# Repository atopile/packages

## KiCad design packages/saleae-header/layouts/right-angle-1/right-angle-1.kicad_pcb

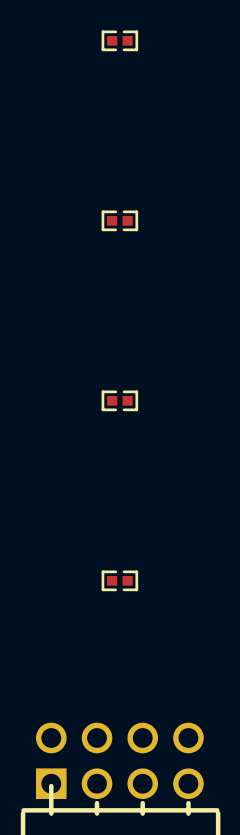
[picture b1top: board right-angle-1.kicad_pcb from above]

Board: 2 copper layers, 5 parts (0 on the bottom side), 5 nets, no tracks yet.

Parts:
R1, R2, R3, R4: 1kΩ ±1% 62.5mW; R0402
U1: HDR-TH_8P-P2.54-H-F-R2-C4-W8.5

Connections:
gnd: U1.2, U1.4, U1.6, U1.8
pins[0]: R1.2, U1.1
pins[2]: R2.2, U1.3
pins[4]: R3.2, U1.5
pins[6]: R4.2, U1.7

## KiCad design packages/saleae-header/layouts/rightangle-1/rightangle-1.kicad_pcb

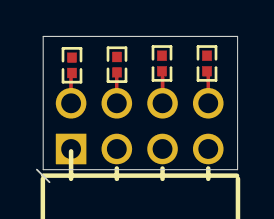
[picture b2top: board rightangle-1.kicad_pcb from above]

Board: 2 copper layers, 11.2 x 8.1 mm, 5 parts (0 on the bottom side), 5 nets.

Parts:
R1, R2, R3, R4: 1000Ω; R0402
U1: HDR-TH_8P-P2.54-H-F-R2-C4-W8.5

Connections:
2: R1.2, U1.2
4: R2.2, U1.4
6: R3.2, U1.6
8: R4.2, U1.8
lv: U1.1, U1.3, U1.5, U1.7

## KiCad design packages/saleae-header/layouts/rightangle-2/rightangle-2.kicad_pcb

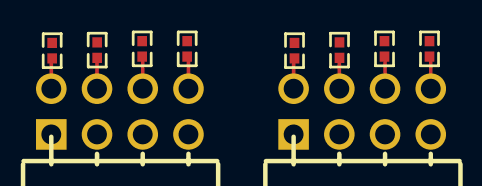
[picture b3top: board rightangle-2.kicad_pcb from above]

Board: 2 copper layers, 10 parts (0 on the bottom side), 10 nets.

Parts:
R1, R2, R3, R4, R5, R6, R7, R8: 1000Ω; R0402
U1, U2: HDR-TH_8P-P2.54-H-F-R2-C4-W8.5

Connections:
2: R1.2, U1.2
4: R2.2, U1.4
6: R3.2, U1.6
8: R4.2, U1.8
headers[1]-2: R5.2, U2.2
headers[1]-4: R6.2, U2.4
headers[1]-6: R7.2, U2.6
headers[1]-8: R8.2, U2.8
headers[1]-reference-lv: U2.1, U2.3, U2.5, U2.7
lv: U1.1, U1.3, U1.5, U1.7

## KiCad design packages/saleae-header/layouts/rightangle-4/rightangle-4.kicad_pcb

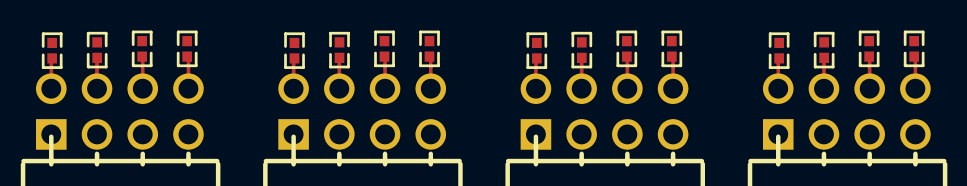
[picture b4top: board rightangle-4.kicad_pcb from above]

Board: 2 copper layers, 20 parts (0 on the bottom side), 20 nets.

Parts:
R1, R2, R3, R4, R5, R6, R7, R8, R9, R10, R11, R12, R13, R14, R15, R16: 1000Ω; R0402
U1, U2, U3, U4: HDR-TH_8P-P2.54-H-F-R2-C4-W8.5

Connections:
2: R1.2, U1.2
4: R2.2, U1.4
6: R3.2, U1.6
8: R4.2, U1.8
headers[1]-2: R5.2, U2.2
headers[1]-4: R6.2, U2.4
headers[1]-6: R7.2, U2.6
headers[1]-8: R8.2, U2.8
headers[1]-reference-lv: U2.1, U2.3, U2.5, U2.7
headers[2]-2: R9.2, U3.2
headers[2]-4: R10.2, U3.4
headers[2]-6: R11.2, U3.6
headers[2]-8: R12.2, U3.8
headers[2]-reference-lv: U3.1, U3.3, U3.5, U3.7
headers[3]-2: R13.2, U4.2
headers[3]-4: R14.2, U4.4
headers[3]-6: R15.2, U4.6
headers[3]-8: R16.2, U4.8
headers[3]-reference-lv: U4.1, U4.3, U4.5, U4.7
lv: U1.1, U1.3, U1.5, U1.7

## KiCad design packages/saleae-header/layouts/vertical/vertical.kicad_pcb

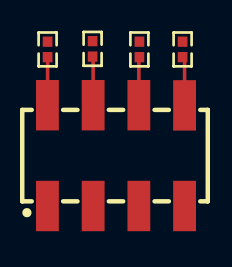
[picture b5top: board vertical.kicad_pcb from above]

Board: 2 copper layers, 5 parts (0 on the bottom side), 5 nets.

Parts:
HDR1: HDR-SMD_8P-P2.54-V-M-R2-C4-LS7.4
R1, R2, R3, R4: 1000Ω; R0402

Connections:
2: HDR1.2, R1.2
4: HDR1.4, R2.2
6: HDR1.6, R3.2
8: HDR1.8, R4.2
lv: HDR1.1, HDR1.3, HDR1.5, HDR1.7

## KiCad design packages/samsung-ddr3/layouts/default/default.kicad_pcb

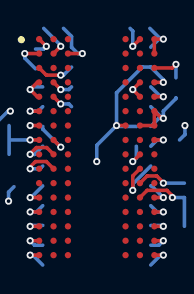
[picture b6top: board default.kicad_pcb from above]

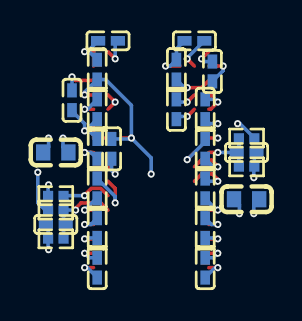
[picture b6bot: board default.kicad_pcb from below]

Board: 4 copper layers, 28 parts (27 on the bottom side), 6 nets.

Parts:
C1, C2, C5, C6, C7, C8, C9, C10, C11, C12, C13, C14, C15, C16, C17, C18, C19, C20, C21, C22: 100nF ±10% 6.3V X7R; C0402
C3, C4: 10µF ±20% 6.3V X5R; C0603
R1: 240Ω ±1% 62.5mW; R0402
R2, R3, R4, R5: 1kΩ ±1% 62.5mW; R0402
U1: TFBGA-96_L13.0-W7.5-R16-C6-P0.80-TL

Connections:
GND: C1.2, C2.2, C3.2, C4.2, C5.2, C6.2, C7.2, C8.2, C9.2, C10.2, C11.2, C12.2, C13.2, C14.2, C15.2, C16.2, C17.2, C18.2, C19.2, C20.2, C21.2, C22.2, R1.2, R2.2, R4.2, U1.A9, U1.B1, U1.B3, U1.B9, U1.D1, U1.D8, U1.E1, U1.E2, U1.E8, U1.F9, U1.G1, U1.G8, U1.G9, U1.J2, U1.J8, U1.M1, U1.M9, U1.P1, U1.P9, U1.T1, U1.T9
ZQ: R1.1, U1.L8
power-VCC: C3.1, C5.1, C6.1, C7.1, C8.1, C9.1, C10.1, C11.1, C12.1, C13.1, R3.1, R5.1, U1.A1, U1.A8, U1.C1, U1.C9, U1.D2, U1.E9, U1.F1, U1.H2, U1.H9
power_internal-VCC: C4.1, C14.1, C15.1, C16.1, C17.1, C18.1, C19.1, C20.1, C21.1, C22.1, U1.B2, U1.D9, U1.G7, U1.K2, U1.K8, U1.N1, U1.N9, U1.R1, U1.R9
vrefca-VCC: C1.1, R2.1, R3.2, U1.M8
vrefdq-VCC: C2.1, R4.1, R5.2, U1.H1
